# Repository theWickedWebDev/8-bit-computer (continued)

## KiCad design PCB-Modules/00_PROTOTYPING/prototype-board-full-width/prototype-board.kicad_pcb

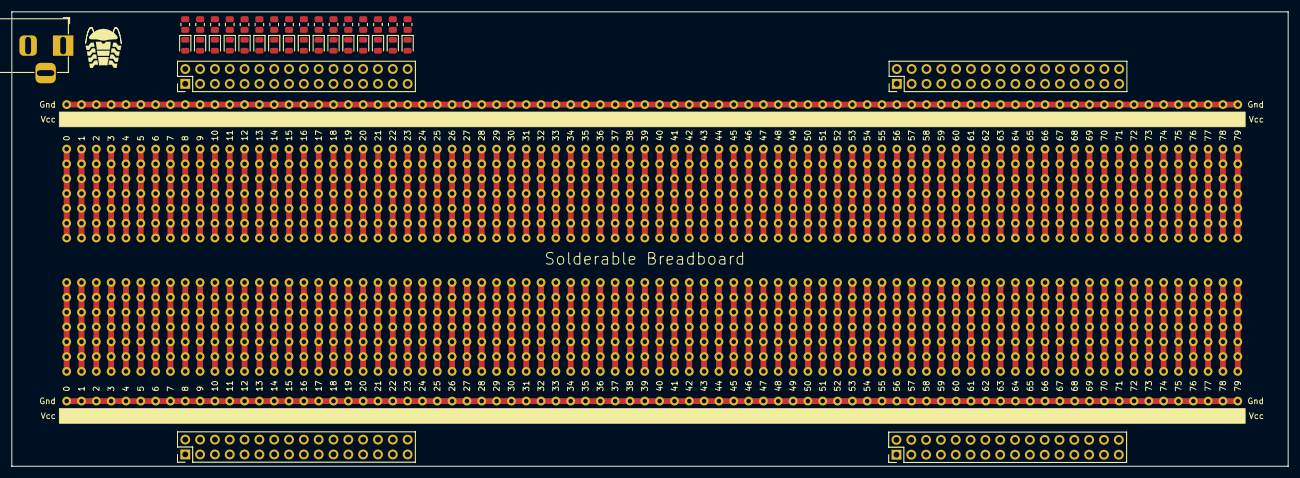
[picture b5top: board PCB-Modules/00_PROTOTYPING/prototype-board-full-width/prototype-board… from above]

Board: 2 copper layers, 218.7 x 77.9 mm, 38 parts (0 on the bottom side), 81 nets.

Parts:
D1, D2, D3, D4, D5, D6, D7, D8, D9, D10, D11, D12, D13, D14, D15, D16: LED; LED_0805_2012Metric
J1: Barrel_Jack_MountingPin; BarrelJack_Horizontal
J2, J3, J4, J5: Conn_02x16_Odd_Even; PinHeader_2x16_P2.54mm_Vertical
R1, R2, R3, R4, R5, R6, R7, R8, R9, R10, R11, R12, R13, R14, R15, R16: R_Small_US; R_0805_2012Metric
U1: breadboard-full; full-breadboard

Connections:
GND: J1.2, R1.2, R2.2, R3.2, R4.2, R5.2, R6.2, R7.2, R8.2, R9.2, R10.2, R11.2, R12.2, R13.2, R14.2, R15.2, R16.2
unnamed: D1.1 (K), R1.1
unnamed: D1.2 (A), J2.1, J2.2
unnamed: D2.1 (K), R2.1
unnamed: D2.2 (A), J2.3, J2.4
unnamed: D3.1 (K), R3.1
unnamed: D3.2 (A), J2.5, J2.6
unnamed: D4.1 (K), R4.1
unnamed: D4.2 (A), J2.7, J2.8
unnamed: D5.1 (K), R5.1
unnamed: D5.2 (A), J2.9, J2.10
unnamed: D6.1 (K), R6.1
unnamed: D6.2 (A), J2.11, J2.12
unnamed: D7.1 (K), R7.1
unnamed: D7.2 (A), J2.13, J2.14
unnamed: D8.1 (K), R8.1
unnamed: D8.2 (A), J2.15, J2.16
unnamed: D9.1 (K), R9.1
unnamed: D9.2 (A), J2.17, J2.18
unnamed: D10.1 (K), R10.1
unnamed: D10.2 (A), J2.19, J2.20
unnamed: D11.1 (K), R11.1
unnamed: D11.2 (A), J2.21, J2.22
unnamed: D12.1 (K), R12.1
unnamed: D12.2 (A), J2.23, J2.24
unnamed: D13.1 (K), R13.1
unnamed: D13.2 (A), J2.25, J2.26
unnamed: D14.1 (K), R14.1
unnamed: D14.2 (A), J2.27, J2.28
unnamed: D15.1 (K), R15.1
unnamed: D15.2 (A), J2.29, J2.30
unnamed: D16.1 (K), R16.1
unnamed: D16.2 (A), J2.31, J2.32
unnamed: J3.1, J3.2
unnamed: J3.3, J3.4
unnamed: J3.5, J3.6
unnamed: J3.7, J3.8
unnamed: J3.9, J3.10
unnamed: J3.11, J3.12
unnamed: J3.13, J3.14
unnamed: J3.15, J3.16
unnamed: J3.17, J3.18
unnamed: J3.19, J3.20
unnamed: J3.21, J3.22
unnamed: J3.23, J3.24
unnamed: J3.25, J3.26
unnamed: J3.27, J3.28
unnamed: J3.29, J3.30
unnamed: J3.31, J3.32
unnamed: J4.1, J4.2
unnamed: J4.3, J4.4
unnamed: J4.5, J4.6
unnamed: J4.7, J4.8
unnamed: J4.9, J4.10
unnamed: J4.11, J4.12
unnamed: J4.13, J4.14
unnamed: J4.15, J4.16
unnamed: J4.17, J4.18
unnamed: J4.19, J4.20
unnamed: J4.21, J4.22
unnamed: J4.23, J4.24
unnamed: J4.25, J4.26
unnamed: J4.27, J4.28
unnamed: J4.29, J4.30
unnamed: J4.31, J4.32
unnamed: J5.1, J5.2
unnamed: J5.3, J5.4
unnamed: J5.5, J5.6
unnamed: J5.7, J5.8
unnamed: J5.9, J5.10
unnamed: J5.11, J5.12
unnamed: J5.13, J5.14
unnamed: J5.15, J5.16
unnamed: J5.17, J5.18
unnamed: J5.19, J5.20
unnamed: J5.21, J5.22
unnamed: J5.23, J5.24
unnamed: J5.25, J5.26
unnamed: J5.27, J5.28
unnamed: J5.29, J5.30
unnamed: J5.31, J5.32

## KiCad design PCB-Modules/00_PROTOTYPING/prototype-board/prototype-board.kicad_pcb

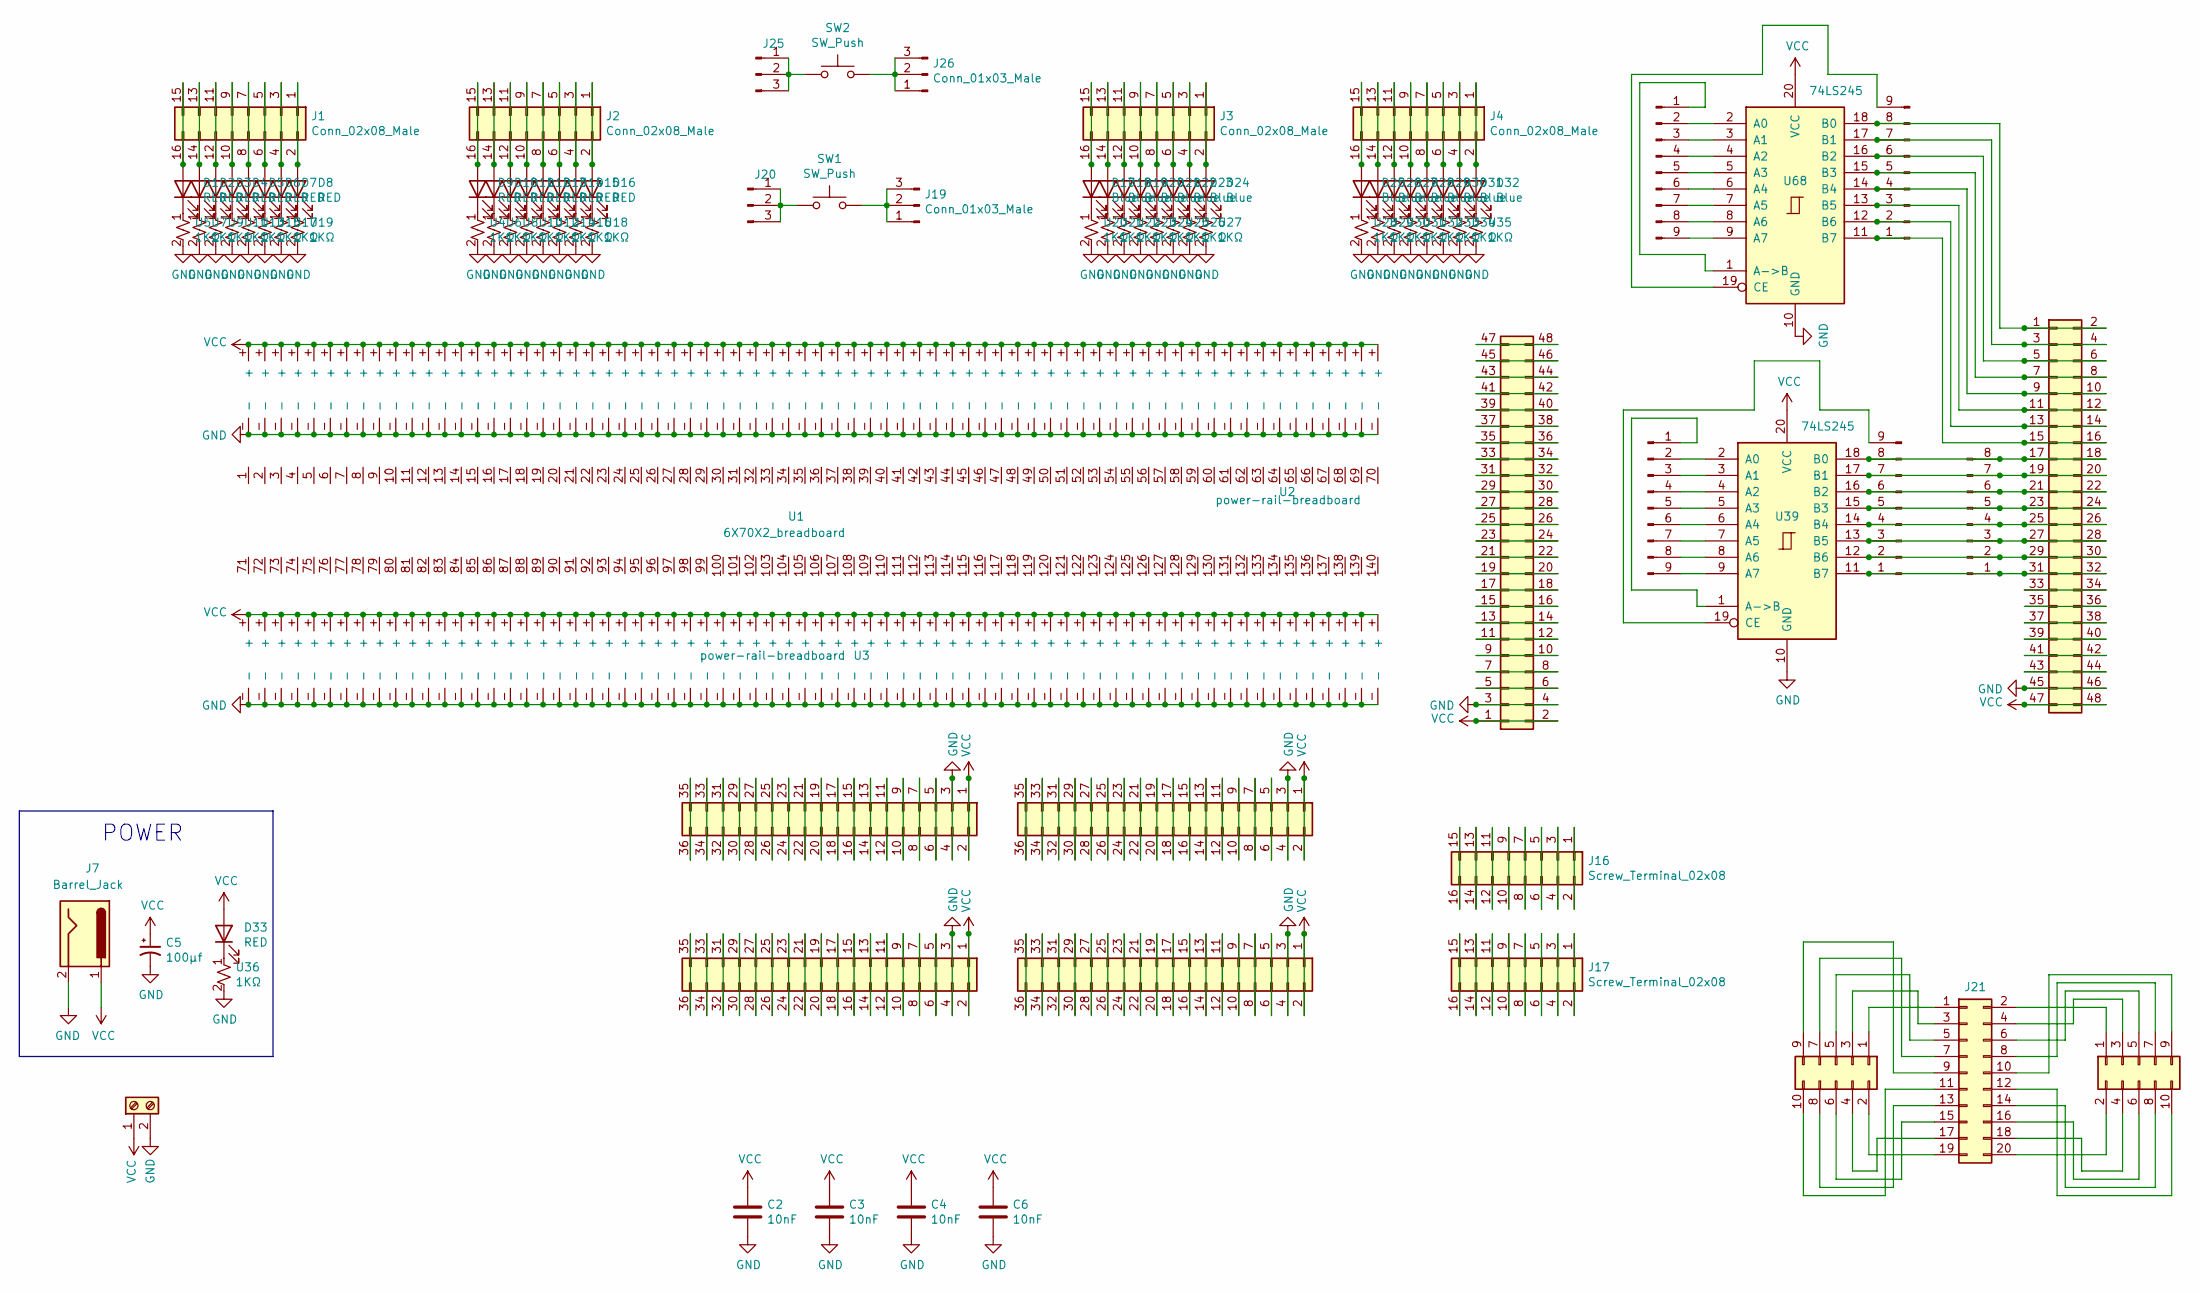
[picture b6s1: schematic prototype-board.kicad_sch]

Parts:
C2, C3, C4, C6: 0603B103K500NT; C_0603_1608Metric
C5: SMD-ECAP-5x5.8; CP_Elec_5x5.8; JLCPCB C140924
D1, D2, D3, D4, D5, D6, D7, D8, D9, D10, D11, D12, D13, D14, D15, D16, D33: NCD0805R1; LED_0805_2012Metric
D17, D18, D19, D20, D21, D22, D23, D24, D25, D26, D27, D28, D29, D30, D31, D32: 19-217/BHC-ZL1M2RY/3T; LED_0603_1608Metric
J1, J2, J3, J4: Conn_02x08_Male; PinHeader_2x08_P2.54mm_Vertical
J5, J6: Conn_02x18_Odd_Even; Breadboard_PinSocket_2x18
J7: Barrel_Jack; BarrelJack_Horizontal
J8, J9: Conn_02x24_Odd_Even; Breadboard_PinHeader_2x24
J10, J11, J12, J13: Conn_01x09_Male; PinHeader_1x09_P2.54mm_Vertical
J14, J15: Conn_02x18_Odd_Even; Breadboard_PinHeader_2x18
J16, J17: Screw_Terminal_02x08; PinSocket_2x08_P2.54mm_Vertical
J18: Screw_Terminal_01x02; TerminalBlock_Phoenix_MKDS-1,5-2_1x02_P5.00mm_Horizontal
J19, J20, J25, J26: Conn_01x03_Male; PinHeader_1x03_P2.54mm_Vertical
J21: Conn_02x20_Odd_Even; IDC-Header_2x10_P2.54mm_Vertical
J22, J23: Conn_02x05_Odd_Even; PinHeader_2x05_P2.54mm_Vertical
J24: Conn_01x08_Male; PinHeader_1x08_P2.54mm_Vertical
SW1, SW2: SW_Push; SW_PUSH_6mm
U1: 6X70X2_breadboard; 6x70
U2, U3: power-rail-breadboard; power-rail-70
U4, U5, U6, U7, U8, U9, U10, U11, U12, U13, U14, U15, U16, U17, U18, U19, U20, U21, U22, U23, U24, U25, U26, U27, U28, U29, U30, U31, U32, U33, U34, U35, U36: 0603WAF1001T5E; R_0603_1608Metric
U39, U68: 74LS245; DIP-20_W7.62mm

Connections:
GND: C2.2, C3.2, C4.2, C5.2, C6.2, J5.3, J5.4, J6.3, J6.4, J7.2, J8.45, J8.46, J9.3, J9.4, J14.3, J14.4, J15.3, J15.4, J18.2, U2.-, U3.-, U4.2, U5.2, U6.2, U7.2, U8.2, U9.2, U10.2, U11.2, U12.2, U13.2, U14.2, U15.2, U16.2, U17.2, U18.2, U19.2, U20.2, U21.2, U22.2, U23.2, U24.2, U25.2, U26.2, U27.2, U28.2, U29.2, U30.2, U31.2, U32.2, U33.2, U34.2, U35.2, U36.2, U39.10 (GND), U68.10 (GND)
unnamed: D1.1 (K), U5.1
unnamed: D1.2 (A), J1.15, J1.16
unnamed: D2.1 (K), U7.1
unnamed: D2.2 (A), J1.13, J1.14
unnamed: D3.1 (K), U9.1
unnamed: D3.2 (A), J1.11, J1.12
unnamed: D4.1 (K), U11.1
unnamed: D4.2 (A), J1.9, J1.10
unnamed: D5.1 (K), U13.1
unnamed: D5.2 (A), J1.7, J1.8
unnamed: D6.1 (K), U15.1
unnamed: D6.2 (A), J1.5, J1.6
unnamed: D7.1 (K), U17.1
unnamed: D7.2 (A), J1.3, J1.4
unnamed: D8.1 (K), U19.1
unnamed: D8.2 (A), J1.1, J1.2
unnamed: D9.1 (K), U4.1
unnamed: D9.2 (A), J2.15, J2.16
unnamed: D10.1 (K), U6.1
unnamed: D10.2 (A), J2.13, J2.14
unnamed: D11.1 (K), U8.1
unnamed: D11.2 (A), J2.11, J2.12
unnamed: D12.1 (K), U10.1
unnamed: D12.2 (A), J2.9, J2.10
unnamed: D13.1 (K), U12.1
unnamed: D13.2 (A), J2.7, J2.8
unnamed: D14.1 (K), U14.1
unnamed: D14.2 (A), J2.5, J2.6
unnamed: D15.1 (K), U16.1
unnamed: D15.2 (A), J2.3, J2.4
unnamed: D16.1 (K), U18.1
unnamed: D16.2 (A), J2.1, J2.2
unnamed: D17.1 (K), U20.1
unnamed: D17.2 (A), J3.15, J3.16
unnamed: D18.1 (K), U21.1
unnamed: D18.2 (A), J3.13, J3.14
unnamed: D19.1 (K), U22.1
unnamed: D19.2 (A), J3.11, J3.12
unnamed: D20.1 (K), U23.1
unnamed: D20.2 (A), J3.9, J3.10
unnamed: D21.1 (K), U24.1
unnamed: D21.2 (A), J3.7, J3.8
unnamed: D22.1 (K), U25.1
unnamed: D22.2 (A), J3.5, J3.6
unnamed: D23.1 (K), U26.1
unnamed: D23.2 (A), J3.3, J3.4
unnamed: D24.1 (K), U27.1
unnamed: D24.2 (A), J3.1, J3.2
unnamed: D25.1 (K), U28.1
unnamed: D25.2 (A), J4.15, J4.16
unnamed: D26.1 (K), U29.1
unnamed: D26.2 (A), J4.13, J4.14
unnamed: D27.1 (K), U30.1
unnamed: D27.2 (A), J4.11, J4.12
unnamed: D28.1 (K), U31.1
unnamed: D28.2 (A), J4.9, J4.10
unnamed: D29.1 (K), U32.1
unnamed: D29.2 (A), J4.7, J4.8
unnamed: D30.1 (K), U33.1
unnamed: D30.2 (A), J4.5, J4.6
unnamed: D31.1 (K), U34.1
unnamed: D31.2 (A), J4.3, J4.4
unnamed: D32.1 (K), U35.1
unnamed: D32.2 (A), J4.1, J4.2
unnamed: D33.1 (K), U36.1
unnamed: J5.5, J5.6
unnamed: J5.7, J5.8
unnamed: J5.9, J5.10
unnamed: J5.11, J5.12
unnamed: J5.13, J5.14
unnamed: J5.15, J5.16
unnamed: J5.17, J5.18
unnamed: J5.19, J5.20
unnamed: J5.21, J5.22
unnamed: J5.23, J5.24
unnamed: J5.25, J5.26
unnamed: J5.27, J5.28
unnamed: J5.29, J5.30
unnamed: J5.31, J5.32
unnamed: J5.33, J5.34
unnamed: J5.35, J5.36
unnamed: J6.5, J6.6
unnamed: J6.7, J6.8
unnamed: J6.9, J6.10
unnamed: J6.11, J6.12
unnamed: J6.13, J6.14
unnamed: J6.15, J6.16
unnamed: J6.17, J6.18
unnamed: J6.19, J6.20
unnamed: J6.21, J6.22
unnamed: J6.23, J6.24
unnamed: J6.25, J6.26
unnamed: J6.27, J6.28
unnamed: J6.29, J6.30
unnamed: J6.31, J6.32
unnamed: J6.33, J6.34
unnamed: J6.35, J6.36
unnamed: J8.33, J8.34
unnamed: J8.35, J8.36
unnamed: J8.37, J8.38
unnamed: J8.39, J8.40
unnamed: J8.41, J8.42
unnamed: J8.43, J8.44
unnamed: J9.5, J9.6
unnamed: J9.7, J9.8
unnamed: J9.9, J9.10
unnamed: J9.11, J9.12
unnamed: J9.13, J9.14
unnamed: J9.15, J9.16
unnamed: J9.17, J9.18
unnamed: J9.19, J9.20
unnamed: J9.21, J9.22
unnamed: J9.23, J9.24
unnamed: J9.25, J9.26
unnamed: J9.27, J9.28
unnamed: J9.29, J9.30
unnamed: J9.31, J9.32
unnamed: J9.33, J9.34
unnamed: J9.35, J9.36
unnamed: J9.37, J9.38
unnamed: J9.39, J9.40
unnamed: J9.41, J9.42
unnamed: J9.43, J9.44
unnamed: J9.45, J9.46
unnamed: J9.47, J9.48
unnamed: J10.1, U68.1 (A->B)
unnamed: J10.2, U68.2 (A0)
unnamed: J10.3, U68.3 (A1)
unnamed: J10.4, U68.4 (A2)
unnamed: J10.5, U68.5 (A3)
unnamed: J10.6, U68.6 (A4)
unnamed: J10.7, U68.7 (A5)
unnamed: J10.8, U68.8 (A6)
unnamed: J10.9, U68.9 (A7)
unnamed: J8.15, J8.16, J11.1, U68.11 (B7)
unnamed: J8.13, J8.14, J11.2, U68.12 (B6)
unnamed: J8.11, J8.12, J11.3, U68.13 (B5)
unnamed: J8.9, J8.10, J11.4, U68.14 (B4)
unnamed: J8.7, J8.8, J11.5, U68.15 (B3)
unnamed: J8.5, J8.6, J11.6, U68.16 (B2)
unnamed: J8.3, J8.4, J11.7, U68.17 (B1)
unnamed: J8.1, J8.2, J11.8, U68.18 (B0)
unnamed: J11.9, U68.19 (CE)
unnamed: J12.1, U39.1 (A->B)
unnamed: J12.2, U39.2 (A0)
unnamed: J12.3, U39.3 (A1)
unnamed: J12.4, U39.4 (A2)
unnamed: J12.5, U39.5 (A3)
unnamed: J12.6, U39.6 (A4)
unnamed: J12.7, U39.7 (A5)
unnamed: J12.8, U39.8 (A6)
unnamed: J12.9, U39.9 (A7)
unnamed: J8.31, J8.32, J13.1, J24.1, U39.11 (B7)
unnamed: J8.29, J8.30, J13.2, J24.2, U39.12 (B6)
unnamed: J8.27, J8.28, J13.3, J24.3, U39.13 (B5)
unnamed: J8.25, J8.26, J13.4, J24.4, U39.14 (B4)
unnamed: J8.23, J8.24, J13.5, J24.5, U39.15 (B3)
unnamed: J8.21, J8.22, J13.6, J24.6, U39.16 (B2)
unnamed: J8.19, J8.20, J13.7, J24.7, U39.17 (B1)
unnamed: J8.17, J8.18, J13.8, J24.8, U39.18 (B0)
unnamed: J13.9, U39.19 (CE)
unnamed: J14.5, J14.6
unnamed: J14.7, J14.8
unnamed: J14.9, J14.10
unnamed: J14.11, J14.12
unnamed: J14.13, J14.14
unnamed: J14.15, J14.16
unnamed: J14.17, J14.18
unnamed: J14.19, J14.20
unnamed: J14.21, J14.22
unnamed: J14.23, J14.24
unnamed: J14.25, J14.26
unnamed: J14.27, J14.28
unnamed: J14.29, J14.30
unnamed: J14.31, J14.32
unnamed: J14.33, J14.34
unnamed: J14.35, J14.36
unnamed: J15.5, J15.6
unnamed: J15.7, J15.8
unnamed: J15.9, J15.10
unnamed: J15.11, J15.12
unnamed: J15.13, J15.14
unnamed: J15.15, J15.16
unnamed: J15.17, J15.18
unnamed: J15.19, J15.20
unnamed: J15.21, J15.22
unnamed: J15.23, J15.24
unnamed: J15.25, J15.26
unnamed: J15.27, J15.28
unnamed: J15.29, J15.30
unnamed: J15.31, J15.32
unnamed: J15.33, J15.34
unnamed: J15.35, J15.36
unnamed: J16.1, J16.2
unnamed: J16.3, J16.4
unnamed: J16.5, J16.6
unnamed: J16.7, J16.8
unnamed: J16.9, J16.10
unnamed: J16.11, J16.12
unnamed: J16.13, J16.14
unnamed: J16.15, J16.16
unnamed: J17.1, J17.2
unnamed: J17.3, J17.4
unnamed: J17.5, J17.6
unnamed: J17.7, J17.8
unnamed: J17.9, J17.10
unnamed: J17.11, J17.12
unnamed: J17.13, J17.14
unnamed: J17.15, J17.16
unnamed: J19.1, J19.2, J19.3, SW1.2
unnamed: J20.1, J20.2, J20.3, SW1.1
unnamed: J21.1, J23.1
unnamed: J21.2, J22.1
unnamed: J21.3, J23.3
unnamed: J21.4, J22.3
unnamed: J21.5, J23.5
unnamed: J21.6, J22.5
unnamed: J21.7, J23.7
unnamed: J21.8, J22.7
unnamed: J21.9, J23.9
unnamed: J21.10, J22.9
unnamed: J21.11, J23.10
unnamed: J21.12, J22.10
unnamed: J21.13, J23.8
unnamed: J21.14, J22.8
unnamed: J21.15, J23.6
unnamed: J21.16, J22.6
unnamed: J21.17, J23.4
unnamed: J21.18, J22.4
unnamed: J21.19, J23.2
unnamed: J21.20, J22.2
unnamed: J25.1, J25.2, J25.3, SW2.1
unnamed: J26.1, J26.2, J26.3, SW2.2
VCC: C2.1, C3.1, C4.1, C5.1, C6.1, D33.2 (A), J5.1, J5.2, J6.1, J6.2, J7.1, J8.47, J8.48, J9.1, J9.2, J14.1, J14.2, J15.1, J15.2, J18.1, U2.+, U3.+, U39.20 (VCC), U68.20 (VCC)

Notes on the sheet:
POWER

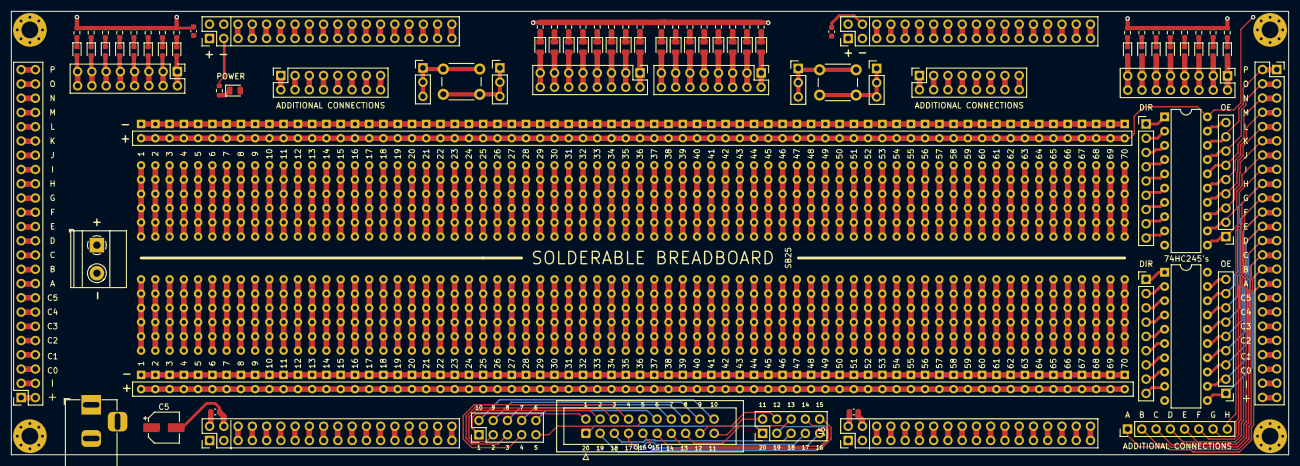
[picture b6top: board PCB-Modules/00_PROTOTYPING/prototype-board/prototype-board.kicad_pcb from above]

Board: 2 copper layers, 227.6 x 79.0 mm, 104 parts (0 on the bottom side), 235 nets.

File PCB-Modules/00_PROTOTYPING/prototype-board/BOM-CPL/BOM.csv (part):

Designator,Value,LibPart,Footprint,Datasheet,C,Description,JCLC,JLCPCB,R,,
C2,0603B103K500NT,JLCPCB:0603B103K500NT,Capacitor_SMD:C_0603_1608Metric,https://datasheet.lcsc.com/lcsc/2102081402_FH-Guangdong-Feng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,10nF,X7R ±10% 50V 10nF 0603 Multilayer Ceramic Capacitors MLCC - SMD/SMT ROHS,C57112,,,,
C3,0603B103K500NT,JLCPCB:0603B103K500NT,Capacitor_SMD:C_0603_1608Metric,https://datasheet.lcsc.com/lcsc/2102081402_FH-Guangdong-Feng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,10nF,X7R ±10% 50V 10nF 0603 Multilayer Ceramic Capacitors MLCC - SMD/SMT ROHS,C57112,,,,
C4,0603B103K500NT,JLCPCB:0603B103K500NT,Capacitor_SMD:C_0603_1608Metric,https://datasheet.lcsc.com/lcsc/2102081402_FH-Guangdong-Feng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,10nF,X7R ±10% 50V 10nF 0603 Multilayer Ceramic Capacitors MLCC - SMD/SMT ROHS,C57112,,,,
C5,SMD-ECAP-5x5.8,Device:CP1_Small,Capacitor_SMD:CP_Elec_5x5.8,https://datasheet.lcsc.com/lcsc/1810010225_Lelon-VZS101M1ATR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,100µf,"- - 5mm 100uF 10V -45℃~+105℃ ±20% 5.8mm 2000hrs 105℃ SMD,5x5.8mm Aluminum Electrolytic Capacitors - SMD ROHS",C140924,C140924,,,
C6,0603B103K500NT,JLCPCB:0603B103K500NT,Capacitor_SMD:C_0603_1608Metric,https://datasheet.lcsc.com/lcsc/2102081402_FH-Guangdong-Feng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,10nF,X7R ±10% 50V 10nF 0603 Multilayer Ceramic Capacitors MLCC - SMD/SMT ROHS,C57112,,,,
D1,NCD0805R1,Device:LED,LED_SMD:LED_0805_2012Metric,~,RED,,C84256,,,,
D2,NCD0805R1,Device:LED,LED_SMD:LED_0805_2012Metric,~,RED,,C84256,,,,
D3,NCD0805R1,Device:LED,LED_SMD:LED_0805_2012Metric,~,RED,,C84256,,,,
D4,NCD0805R1,Device:LED,LED_SMD:LED_0805_2012Metric,~,RED,,C84256,,,,
D5,NCD0805R1,Device:LED,LED_SMD:LED_0805_2012Metric,~,RED,,C84256,,,,
D6,NCD0805R1,Device:LED,LED_SMD:LED_0805_2012Metric,~,RED,,C84256,,,,
D7,NCD0805R1,Device:LED,LED_SMD:LED_0805_2012Metric,~,RED,,C84256,,,,
D8,NCD0805R1,Device:LED,LED_SMD:LED_0805_2012Metric,~,RED,,C84256,,,,
D9,NCD0805R1,Device:LED,LED_SMD:LED_0805_2012Metric,~,RED,,C84256,,,,
D10,NCD0805R1,Device:LED,LED_SMD:LED_0805_2012Metric,~,RED,,C84256,,,,
D11,NCD0805R1,Device:LED,LED_SMD:LED_0805_2012Metric,~,RED,,C84256,,,,
D12,NCD0805R1,Device:LED,LED_SMD:LED_0805_2012Metric,~,RED,,C84256,,,,
D13,NCD0805R1,Device:LED,LED_SMD:LED_0805_2012Metric,~,RED,,C84256,,,,
D14,NCD0805R1,Device:LED,LED_SMD:LED_0805_2012Metric,~,RED,,C84256,,,,
D15,NCD0805R1,Device:LED,LED_SMD:LED_0805_2012Metric,~,RED,,C84256,,,,
D16,NCD0805R1,Device:LED,LED_SMD:LED_0805_2012Metric,~,RED,,C84256,,,,
D17,19-217/BHC-ZL1M2RY/3T,Device:LED,LED_SMD:LED_0603_1608Metric,~,Blue,Blue 465~475nm 0603 Light Emitting Diodes (LED) ROHS,C72041,,,,
D18,19-217/BHC-ZL1M2RY/3T,Device:LED,LED_SMD:LED_0603_1608Metric,~,Blue,Blue 465~475nm 0603 Light Emitting Diodes (LED) ROHS,C72041,,,,
D19,19-217/BHC-ZL1M2RY/3T,Device:LED,LED_SMD:LED_0603_1608Metric,~,Blue,Blue 465~475nm 0603 Light Emitting Diodes (LED) ROHS,C72041,,,,
D20,19-217/BHC-ZL1M2RY/3T,Device:LED,LED_SMD:LED_0603_1608Metric,~,Blue,Blue 465~475nm 0603 Light Emitting Diodes (LED) ROHS,C72041,,,,
D21,19-217/BHC-ZL1M2RY/3T,Device:LED,LED_SMD:LED_0603_1608Metric,~,Blue,Blue 465~475nm 0603 Light Emitting Diodes (LED) ROHS,C72041,,,,
D22,19-217/BHC-ZL1M2RY/3T,Device:LED,LED_SMD:LED_0603_1608Metric,~,Blue,Blue 465~475nm 0603 Light Emitting Diodes (LED) ROHS,C72041,,,,
D23,19-217/BHC-ZL1M2RY/3T,Device:LED,LED_SMD:LED_0603_1608Metric,~,Blue,Blue 465~475nm 0603 Light Emitting Diodes (LED) ROHS,C72041,,,,
D24,19-217/BHC-ZL1M2RY/3T,Device:LED,LED_SMD:LED_0603_1608Metric,~,Blue,Blue 465~475nm 0603 Light Emitting Diodes (LED) ROHS,C72041,,,,
D25,19-217/BHC-ZL1M2RY/3T,Device:LED,LED_SMD:LED_0603_1608Metric,~,Blue,Blue 465~475nm 0603 Light Emitting Diodes (LED) ROHS,C72041,,,,
D26,19-217/BHC-ZL1M2RY/3T,Device:LED,LED_SMD:LED_0603_1608Metric,~,Blue,Blue 465~475nm 0603 Light Emitting Diodes (LED) ROHS,C72041,,,,
D27,19-217/BHC-ZL1M2RY/3T,Device:LED,LED_SMD:LED_0603_1608Metric,~,Blue,Blue 465~475nm 0603 Light Emitting Diodes (LED) ROHS,C72041,,,,
D28,19-217/BHC-ZL1M2RY/3T,Device:LED,LED_SMD:LED_0603_1608Metric,~,Blue,Blue 465~475nm 0603 Light Emitting Diodes (LED) ROHS,C72041,,,,
D29,19-217/BHC-ZL1M2RY/3T,Device:LED,LED_SMD:LED_0603_1608Metric,~,Blue,Blue 465~475nm 0603 Light Emitting Diodes (LED) ROHS,C72041,,,,
D30,19-217/BHC-ZL1M2RY/3T,Device:LED,LED_SMD:LED_0603_1608Metric,~,Blue,Blue 465~475nm 0603 Light Emitting Diodes (LED) ROHS,C72041,,,,
D31,19-217/BHC-ZL1M2RY/3T,Device:LED,LED_SMD:LED_0603_1608Metric,~,Blue,Blue 465~475nm 0603 Light Emitting Diodes (LED) ROHS,C72041,,,,
D32,19-217/BHC-ZL1M2RY/3T,Device:LED,LED_SMD:LED_0603_1608Metric,~,Blue,Blue 465~475nm 0603 Light Emitting Diodes (LED) ROHS,C72041,,,,
D33,NCD0805R1,Device:LED,LED_SMD:LED_0805_2012Metric,~,RED,,C84256,,,,
J1,Conn_02x08_Male,Connector_Generic:Conn_02x08_Odd_Even,Connector_PinHeader_2.54mm:PinHeader_2x08_P2.54mm_Vertical,~,,,,,,,
J2,Conn_02x08_Male,Connector_Generic:Conn_02x08_Odd_Even,Connector_PinHeader_2.54mm:PinHeader_2x08_P2.54mm_Vertical,~,,,,,,,
J3,Conn_02x08_Male,Connector_Generic:Conn_02x08_Odd_Even,Connector_PinHeader_2.54mm:PinHeader_2x08_P2.54mm_Vertical,~,,,,,,,
J4,Conn_02x08_Male,Connector_Generic:Conn_02x08_Odd_Even,Connector_PinHeader_2.54mm:PinHeader_2x08_P2.54mm_Vertical,~,,,,,,,
J5,Conn_02x18_Odd_Even,Connector_Generic:Conn_02x18_Odd_Even,Connector_PinHeader_2.54mm:PinHeader_2x18_P2.54mm_Vertical,~,,,,,,,
J6,Conn_02x18_Odd_Even,Connector_Generic:Conn_02x18_Odd_Even,Connector_PinHeader_2.54mm:PinHeader_2x18_P2.54mm_Vertical,~,,,,,,,
J7,Barrel_Jack,Connector:Barrel_Jack,Connector_BarrelJack:BarrelJack_Horizontal,~,,,,,,,
J8,Conn_02x24_Odd_Even,Connector_Generic:Conn_02x24_Odd_Even,Connector_PinHeader_2.54mm:PinHeader_2x24_P2.54mm_Vertical,~,,,,,,,
J9,Conn_02x24_Odd_Even,Connector_Generic:Conn_02x24_Odd_Even,Connector_PinHeader_2.54mm:PinHeader_2x24_P2.54mm_Vertical,~,,,,,,,
J10,Conn_01x09_Male,Connector:Conn_01x09_Male,Connector_PinHeader_2.54mm:PinHeader_1x09_P2.54mm_Vertical,~,,,,,,,
J11,Conn_01x09_Male,Connector:Conn_01x09_Male,Connector_PinHeader_2.54mm:PinHeader_1x09_P2.54mm_Vertical,~,,,,,,,
J12,Conn_01x09_Male,Connector:Conn_01x09_Male,Connector_PinHeader_2.54mm:PinHeader_1x09_P2.54mm_Vertical,~,,,,,,,
J13,Conn_01x09_Male,Connector:Conn_01x09_Male,Connector_PinHeader_2.54mm:PinHeader_1x09_P2.54mm_Vertical,~,,,,,,,
J14,Conn_02x18_Odd_Even,Connector_Generic:Conn_02x18_Odd_Even,Connector_PinHeader_2.54mm:PinHeader_2x18_P2.54mm_Vertical,~,,,,,,,
J15,Conn_02x18_Odd_Even,Connector_Generic:Conn_02x18_Odd_Even,Connector_PinHeader_2.54mm:PinHeader_2x18_P2.54mm_Vertical,~,,,,,,,
J16,Screw_Terminal_02x08,Connector_Generic:Conn_02x08_Odd_Even,Connector_PinSocket_2.54mm:PinSocket_2x08_P2.54mm_Vertical,~,,,,,,,
J17,Screw_Terminal_02x08,Connector_Generic:Conn_02x08_Odd_Even,Connector_PinSocket_2.54mm:PinSocket_2x08_P2.54mm_Vertical,~,,,,,,,
J18,Screw_Terminal_01x02,Connector:Screw_Terminal_01x02,"TerminalBlock_Phoenix:TerminalBlock_Phoenix_MKDS-1,5-2_1x02_P5.00mm_Horizontal",~,,,,,,,
J19,Conn_01x03_Male,Connector:Conn_01x03_Male,Connector_PinHeader_2.54mm:PinHeader_1x03_P2.54mm_Vertical,~,,,,,,,
J20,Conn_01x03_Male,Connector:Conn_01x03_Male,Connector_PinHeader_2.54mm:PinHeader_1x03_P2.54mm_Vertical,~,,,,,,,
J21,Conn_02x20_Odd_Even,Connector_Generic:Conn_02x10_Odd_Even,Connector_IDC:IDC-Header_2x10_P2.54mm_Vertical,~,,,,,,,
J22,Conn_02x05_Odd_Even,Connector_Generic:Conn_02x05_Odd_Even,Connector_PinHeader_2.54mm:PinHeader_2x05_P2.54mm_Vertical,~,,,,,,,
J23,Conn_02x05_Odd_Even,Connector_Generic:Conn_02x05_Odd_Even,Connector_PinHeader_2.54mm:PinHeader_2x05_P2.54mm_Vertical,~,,,,,,,
J24,Conn_01x08_Male,Connector:Conn_01x08_Male,Connector_PinHeader_2.54mm:PinHeader_1x08_P2.54mm_Vertical,~,,,,,,,
J25,Conn_01x03_Male,Connector:Conn_01x03_Male,Connector_PinHeader_2.54mm:PinHeader_1x03_P2.54mm_Vertical,~,,,,,,,
J26,Conn_01x03_Male,Connector:Conn_01x03_Male,Connector_PinHeader_2.54mm:PinHeader_1x03_P2.54mm_Vertical,~,,,,,,,
SW1,SW_Push,Switch:SW_Push,Button_Switch_THT:SW_PUSH_6mm,~,,,,,,,
SW2,SW_Push,Switch:SW_Push,Button_Switch_THT:SW_PUSH_6mm,~,,,,,,,
U1,6X70X2_breadboard,Connector:6X70X2_breadboard,breadboard-prototype:6x70,,,,,,,,
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
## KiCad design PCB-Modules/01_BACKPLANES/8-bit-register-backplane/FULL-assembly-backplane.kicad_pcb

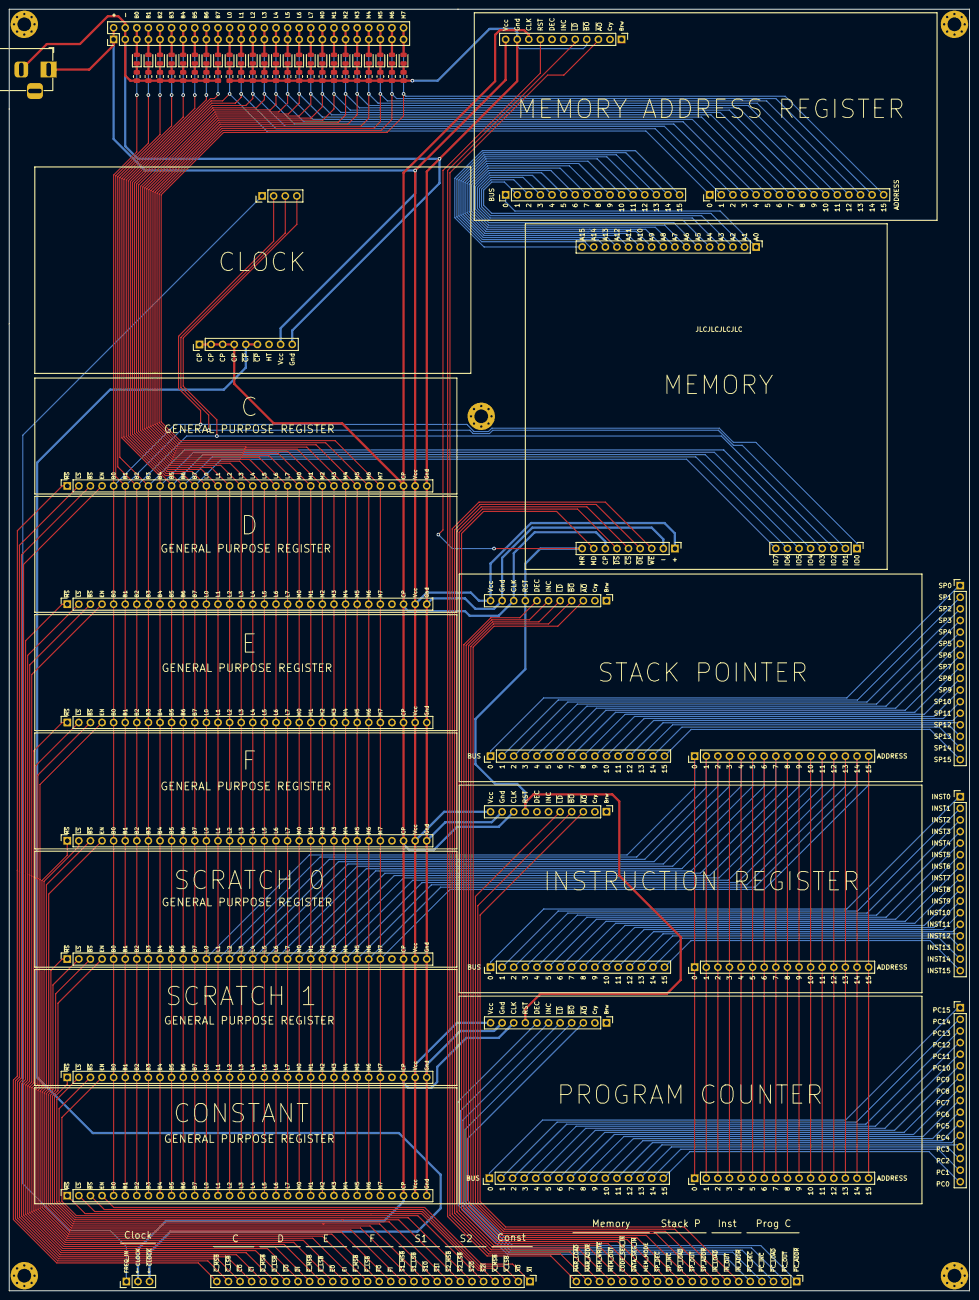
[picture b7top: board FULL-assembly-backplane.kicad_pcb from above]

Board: 2 copper layers, 210.3 x 280.7 mm, 80 parts (0 on the bottom side), 166 nets.

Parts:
D1, D2, D3, D4, D5, D6, D7, D8, D9, D10, D11, D12, D13, D14, D15, D16, D17, D18, D19, D20, D21, D22, D23, D24: LED; LED_0805_2012Metric
J1: Conn_01x28; PinHeader_1x28_P2.54mm_Vertical
J2: Conn_01x20; PinHeader_1x20_P2.54mm_Vertical
J3: Conn_01x08; PinHeader_1x08_P2.54mm_Vertical
J4, J5: Conn_01x09; PinHeader_1x09_P2.54mm_Vertical
J6, J7, J8, J9, J10, J11, J12, J13, J14, J15, J16, J17: Conn_01x16; PinHeader_1x16_P2.54mm_Vertical
J18, J19, J20, J21: Conn_01x11; PinHeader_1x11_P2.54mm_Vertical
J22: Conn_01x04; PinHeader_1x04_P2.54mm_Vertical
J24: Conn_01x03; PinHeader_1x03_P2.54mm_Vertical
J25, J26, J32, J33, J34, J35, J36: Conn_01x32; PinSocket_1x32_P2.54mm_Vertical
J37: Conn_01x26; PinHeader_2x26_P2.54mm_Vertical
J43: Barrel_Jack; BarrelJack_Horizontal
R1, R2, R3, R4, R5, R6, R7, R8, R9, R10, R11, R12, R13, R14, R15, R16, R17, R18, R19, R20, R21, R22, R23, R24: R_US; R_0805_2012Metric

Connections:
/IN_B0: J10.1, J11.1
/IN_B1: J10.2, J11.2
/IN_B2: J10.3, J11.3
/IN_B3: J10.4, J11.4
/IN_B4: J10.5, J11.5
/IN_B5: J10.6, J11.6
/IN_B6: J10.7, J11.7
/IN_B7: J10.8, J11.8
/IN_B8: J10.9, J11.9
/IN_B9: J10.10, J11.10
/IN_B10: J10.11, J11.11
/IN_B11: J10.12, J11.12
/IN_B12: J10.13, J11.13
/IN_B13: J10.14, J11.14
/IN_B14: J10.15, J11.15
/IN_B15: J10.16, J11.16
/MAR_B0: J16.1, J17.1
/MAR_B1: J16.2, J17.2
/MAR_B2: J16.3, J17.3
/MAR_B3: J16.4, J17.4
/MAR_B4: J16.5, J17.5
/MAR_B5: J16.6, J17.6
/MAR_B6: J16.7, J17.7
/MAR_B7: J16.8, J17.8
/MAR_B8: J16.9, J17.9
/MAR_B9: J16.10, J17.10
/MAR_B10: J16.11, J17.11
/MAR_B11: J16.12, J17.12
/MAR_B12: J16.13, J17.13
/MAR_B13: J16.14, J17.14
/MAR_B14: J16.15, J17.15
/MAR_B15: J16.16, J17.16
/PC_B0: J13.1, J14.1
/PC_B1: J13.2, J14.2
/PC_B2: J13.3, J14.3
/PC_B3: J13.4, J14.4
/PC_B4: J13.5, J14.5
/PC_B5: J13.6, J14.6
/PC_B6: J13.7, J14.7
/PC_B7: J13.8, J14.8
/PC_B8: J13.9, J14.9
/PC_B9: J13.10, J14.10
/PC_B10: J13.11, J14.11
/PC_B11: J13.12, J14.12
/PC_B12: J13.13, J14.13
/PC_B13: J13.14, J14.14
/PC_B14: J13.15, J14.15
/PC_B15: J13.16, J14.16
/SP_B0: J7.1, J8.1
/SP_B1: J7.2, J8.2
/SP_B2: J7.3, J8.3
/SP_B3: J7.4, J8.4
/SP_B4: J7.5, J8.5
/SP_B5: J7.6, J8.6
/SP_B6: J7.7, J8.7
/SP_B7: J7.8, J8.8
/SP_B8: J7.9, J8.9
/SP_B9: J7.10, J8.10
/SP_B10: J7.11, J8.11
/SP_B11: J7.12, J8.12
/SP_B12: J7.13, J8.13
/SP_B13: J7.14, J8.14
/SP_B14: J7.15, J8.15
/SP_B15: J7.16, J8.16
BUS0: D1.2, J3.1, J22.2, J25.5, J26.5, J32.5, J33.5, J34.5, J35.5, J36.5, J37.5, J37.6
BUS1: D2.2, J3.2, J22.3, J25.6, J26.6, J32.6, J33.6, J34.6, J35.6, J36.6, J37.7, J37.8
BUS2: D3.2, J3.3, J22.4, J25.7, J26.7, J32.7, J33.7, J34.7, J35.7, J36.7, J37.9, J37.10
BUS3: D4.2, J3.4, J25.8, J26.8, J32.8, J33.8, J34.8, J35.8, J36.8, J37.11, J37.12
BUS4: D5.2, J3.5, J25.9, J26.9, J32.9, J33.9, J34.9, J35.9, J36.9, J37.13, J37.14
BUS5: D6.2, J3.6, J25.10, J26.10, J32.10, J33.10, J34.10, J35.10, J36.10, J37.15, J37.16
BUS6: D7.2, J3.7, J25.11, J26.11, J32.11, J33.11, J34.11, J35.11, J36.11, J37.17, J37.18
BUS7: D8.2, J3.8, J25.12, J26.12, J32.12, J33.12, J34.12, J35.12, J36.12, J37.19, J37.20
CLOCK: J4.7, J5.1, J5.2, J5.3, J5.4, J18.9, J19.9, J20.9, J21.9, J24.2, J25.30, J26.30, J32.30, J33.30, J34.30, J35.30, J36.30
FREQ_IN: J22.1, J24.1
GND: J4.2, J5.9, J18.10, J19.10, J20.4, J20.10, J21.10, J25.32, J26.32, J32.32, J33.32, J34.32, J35.32, J36.32, J37.3, J37.4, J43.2, R1.2, R2.2, R3.2, R4.2, R5.2, R6.2, R7.2, R8.2, R9.2, R10.2, R11.2, R12.2, R13.2, R14.2, R15.2, R16.2, R17.2, R18.2, R19.2, R20.2, R21.2, R22.2, R23.2, R24.2
I_C: J1.25, J32.4
I_CONST: J1.1, J26.4
I_D: J1.21, J33.4
I_E: J1.17, J34.4
I_F: J1.13, J35.4
I_SCR_0: J1.9, J36.4
I_SCR_1: J1.5, J25.4
L0: D9.2, J6.1, J9.1, J12.1, J15.1, J25.13, J26.13, J32.13, J33.13, J34.13, J35.13, J36.13, J37.21, J37.22
L1: D10.2, J6.2, J9.2, J12.2, J15.2, J25.14, J26.14, J32.14, J33.14, J34.14, J35.14, J36.14, J37.23, J37.24
L2: D11.2, J6.3, J9.3, J12.3, J15.3, J25.15, J26.15, J32.15, J33.15, J34.15, J35.15, J36.15, J37.25, J37.26
L3: D12.2, J6.4, J9.4, J12.4, J15.4, J25.16, J26.16, J32.16, J33.16, J34.16, J35.16, J36.16, J37.27, J37.28
L4: D13.2, J6.5, J9.5, J12.5, J15.5, J25.17, J26.17, J32.17, J33.17, J34.17, J35.17, J36.17, J37.29, J37.30
L5: D14.2, J6.6, J9.6, J12.6, J15.6, J25.18, J26.18, J32.18, J33.18, J34.18, J35.18, J36.18, J37.31, J37.32
L6: D15.2, J6.7, J9.7, J12.7, J15.7, J25.19, J26.19, J32.19, J33.19, J34.19, J35.19, J36.19, J37.33, J37.34
L7: D16.2, J6.8, J9.8, J12.8, J15.8, J25.20, J26.20, J32.20, J33.20, J34.20, J35.20, J36.20, J37.35, J37.36
LSB_C: J1.27, J32.2
LSB_CONST: J1.3, J26.2
LSB_D: J1.23, J33.2
LSB_E: J1.19, J34.2
LSB_F: J1.15, J35.2
LSB_SCR_0: J1.11, J36.2
LSB_SCR_1: J1.7, J25.2
M0: D17.2, J6.9, J9.9, J12.9, J15.9, J25.21, J26.21, J32.21, J33.21, J34.21, J35.21, J36.21, J37.37, J37.38
M1: D18.2, J6.10, J9.10, J12.10, J15.10, J25.22, J26.22, J32.22, J33.22, J34.22, J35.22, J36.22, J37.39, J37.40
M2: D19.2, J6.11, J9.11, J12.11, J15.11, J25.23, J26.23, J32.23, J33.23, J34.23, J35.23, J36.23, J37.41, J37.42
M3: D20.2, J6.12, J9.12, J12.12, J15.12, J25.24, J26.24, J32.24, J33.24, J34.24, J35.24, J36.24, J37.43, J37.44
M4: D21.2, J6.13, J9.13, J12.13, J15.13, J25.25, J26.25, J32.25, J33.25, J34.25, J35.25, J36.25, J37.45, J37.46
M5: D22.2, J6.14, J9.14, J12.14, J15.14, J25.26, J26.26, J32.26, J33.26, J34.26, J35.26, J36.26, J37.47, J37.48
M6: D23.2, J6.15, J9.15, J12.15, J15.15, J25.27, J26.27, J32.27, J33.27, J34.27, J35.27, J36.27, J37.49, J37.50
M7: D24.2, J6.16, J9.16, J12.16, J15.16, J25.28, J26.28, J32.28, J33.28, J34.28, J35.28, J36.28, J37.51, J37.52
MODE: J2.14, J4.8
MSB_C: J1.28, J32.1
MSB_CONST: J1.4, J26.1
MSB_D: J1.24, J33.1
MSB_E: J1.20, J34.1
MSB_F: J1.16, J35.1
MSB_SCR_0: J1.12, J36.1
MSB_SCR_1: J1.8, J25.1
unnamed: D1.1, R1.1
unnamed: D2.1, R2.1
unnamed: D3.1, R3.1
unnamed: D4.1, R4.1
unnamed: D5.1, R5.1
unnamed: D6.1, R6.1
unnamed: D7.1, R7.1
unnamed: D8.1, R8.1
unnamed: D9.1, R9.1
unnamed: D10.1, R10.1
unnamed: D11.1, R11.1
unnamed: D12.1, R12.1
unnamed: D13.1, R13.1
unnamed: D14.1, R14.1
unnamed: D15.1, R15.1
unnamed: D16.1, R16.1
unnamed: D17.1, R17.1
unnamed: D18.1, R18.1
unnamed: D19.1, R19.1
unnamed: D20.1, R20.1
unnamed: D21.1, R21.1
unnamed: D22.1, R22.1
unnamed: D23.1, R23.1
unnamed: D24.1, R24.1
O_C: J1.26, J32.3
O_CONST: J1.2, J26.3
O_D: J1.22, J33.3
O_E: J1.18, J34.3
O_F: J1.14, J35.3
O_SCR_0: J1.10, J36.3
O_SCR_1: J1.6, J25.3
PC_DEC: J2.5, J21.7
PC_INC: J2.4, J21.6
RESET: J4.9, J18.8, J19.8, J20.8, J21.8
SP_DEC: J2.13, J18.7
SP_INC: J2.12, J18.6
VCC: J4.1, J5.8, J18.11, J19.11, J20.11, J21.11, J25.31, J26.31, J32.31, J33.31, J34.31, J35.31, J36.31, J37.1, J37.2, J43.1
~CLOCK: J5.5, J5.6, J24.3
~CS: J2.16, J4.5
~DS: J2.15, J4.6
~IN_ADDR: J2.6, J19.3
~IN_BO: J2.7, J19.4
~IN_LD: J2.8, J19.5
~LD_STACK_P: J2.11, J18.5
~MAR_ADDR: J2.19, J20.3
~MAR_LD: J2.20, J20.5
~OE: J2.17, J4.4
~PC_ADDR: J2.1, J21.3
~PC_BO: J2.2, J21.4
~PC_LD: J2.3, J21.5
~SP_ADDR: J2.9, J18.3
~SP_BO: J2.10, J18.4
~WE: J2.18, J4.3
